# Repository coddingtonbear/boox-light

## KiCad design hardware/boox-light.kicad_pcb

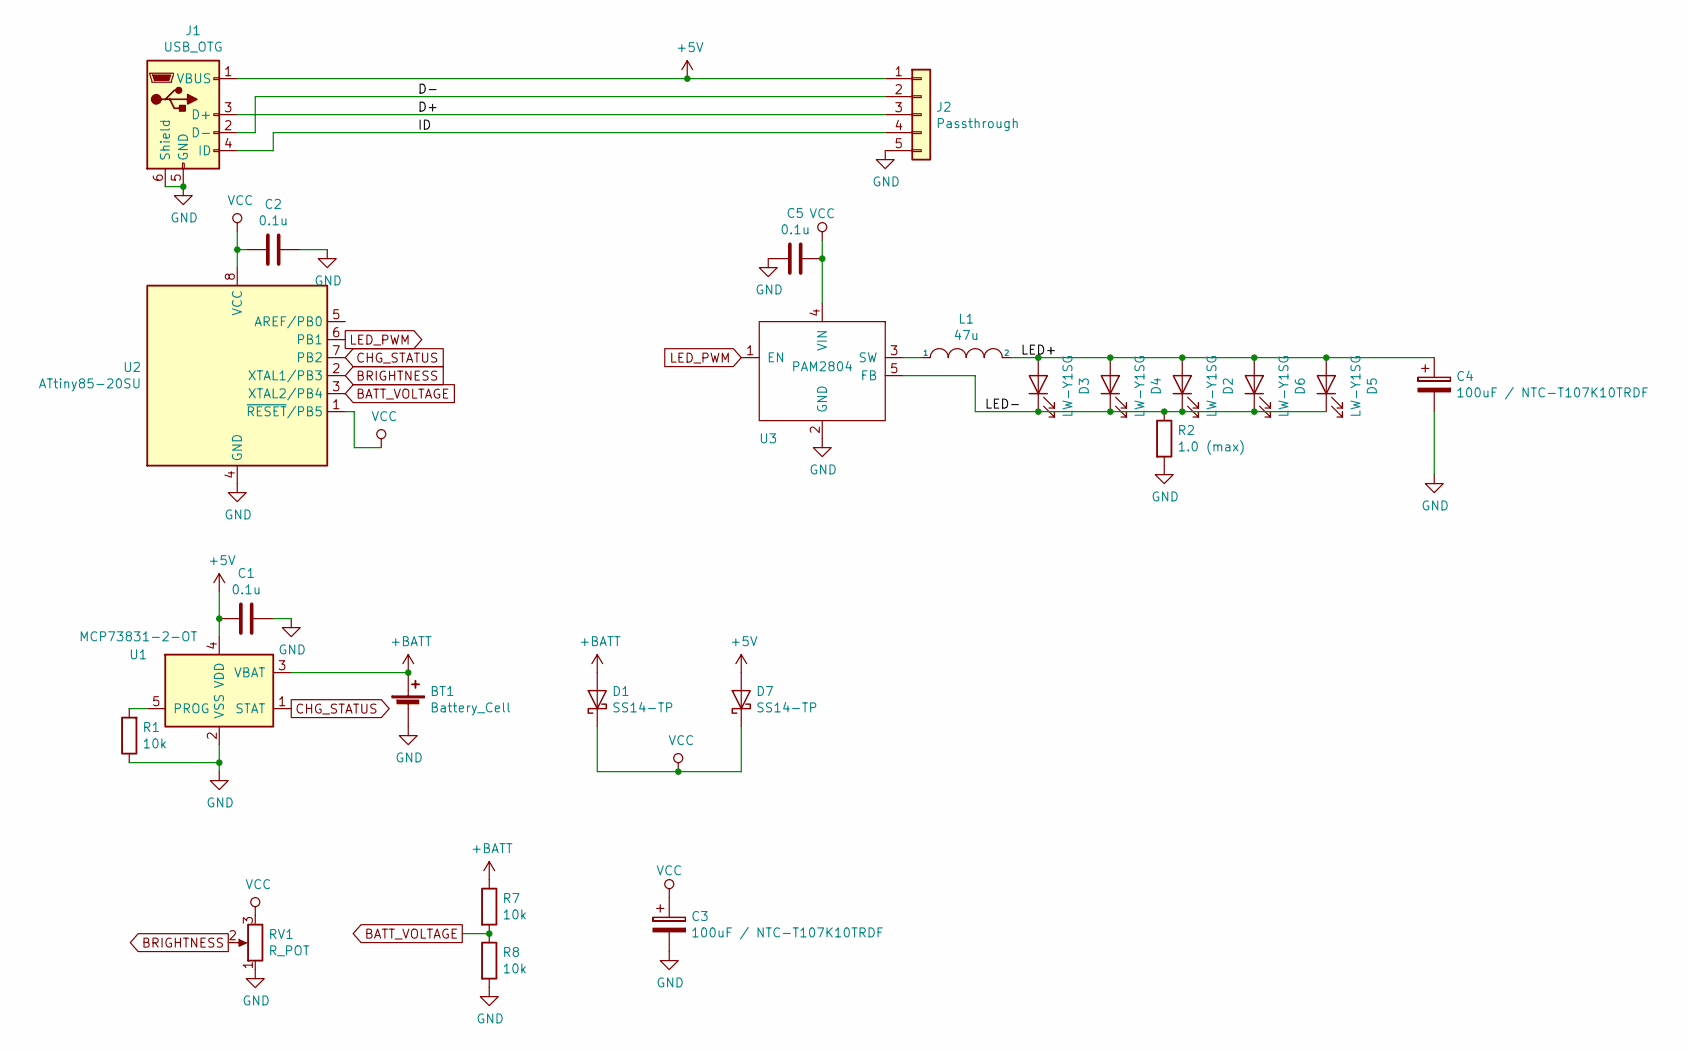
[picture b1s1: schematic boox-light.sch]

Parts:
BT1: Battery_Cell; JST_EH_B02B-EH-A_02x2.50mm_Straight_LargePads
C1, C2, C5: 0.1u; 0805_Milling
C3, C4: 100uF / NTC-T107K10TRDF; CP_Tantalum_Case-D_EIA-7343-31_Milling
D1, D7: SS14-TP; DO-214AC
D2, D3, D4, D5, D6: LW-Y1SG; MICRO_SIDELED_2808
J1: USB_OTG; UJ2-MIBH-4-SMT
J2: Passthrough; JST_XH_B05B-XH-A_05x2.50mm_Straight_LargePads
L1: 47u; L_Bourns-SRN4018
R1, R7, R8: 10k; 0805_Milling
R2: 1.0 (max); 0805_Milling
RV1: R_POT; SV01_Murata_Pot
U1: MCP73831-2-OT; SOT-23-5
U2: ATtiny85-20SU; SOIJ-8_5.3x5.3mm_P1.27mm
U3: PAM2804; TSOT-23-5_HandSoldering

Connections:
+5V: C1.2, D7.2 (A), J1.1 (VBUS), J2.1, U1.4 (VDD)
+BATT: BT1.1 (+), D1.2 (A), R7.1, U1.3 (VBAT)
/D+: J1.3 (D+), J2.3
/D-: J1.2 (D-), J2.2
/ID: J1.4 (ID), J2.4
/LED+: C4.1, D2.2 (A), D3.2 (A), D4.2 (A), D5.2 (A), D6.2 (A), L1.2
/LED-: D2.1 (K), D3.1 (K), D4.1 (K), D5.1 (K), D6.1 (K), R2.1, U3.5 (FB)
BATT_VOLTAGE: R7.2, R8.1, U2.3 (XTAL2/PB4)
BRIGHTNESS: RV1.2, U2.2 (XTAL1/PB3)
CHG_STATUS: U1.1 (STAT), U2.7 (PB2)
GND: BT1.2 (-), C1.1, C2.1, C3.2, C4.2, C5.2, J1.5 (GND), J1.6 (Shield), J2.5, R1.1, R2.2, R8.2, RV1.1, U1.2 (VSS), U2.4 (GND), U3.2 (GND)
LED_PWM: U2.6 (PB1), U3.1 (EN)
unnamed: L1.1, U3.3 (SW)
unnamed: R1.2, U1.5 (PROG)
VCC: C2.2, C3.1, C5.1, D1.1 (K), D7.1 (K), RV1.3, U2.1 (~RESET~/PB5), U2.8 (VCC), U3.4 (VIN)

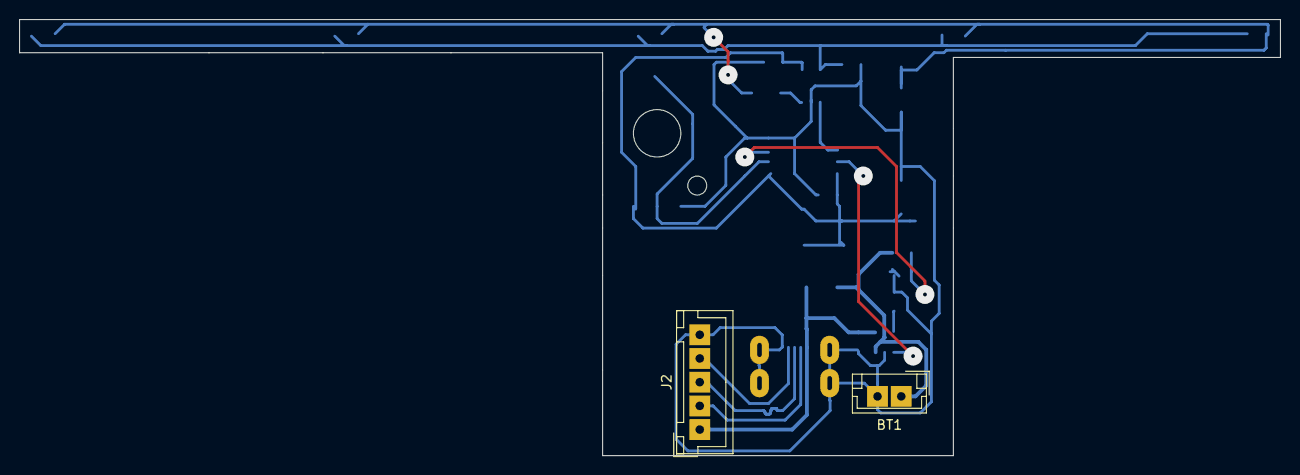
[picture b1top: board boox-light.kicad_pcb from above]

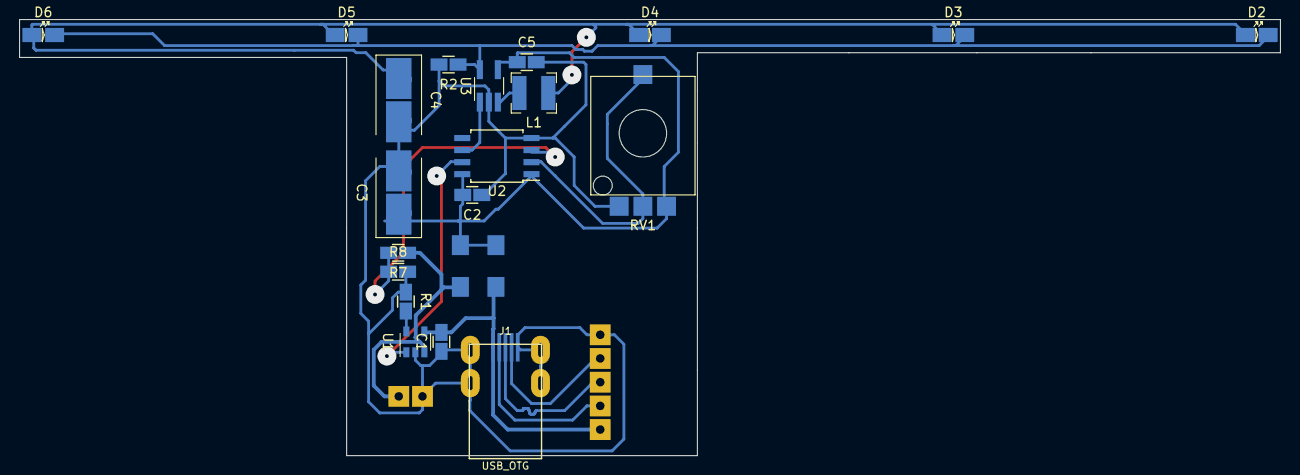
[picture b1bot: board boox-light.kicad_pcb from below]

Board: 2 copper layers, 133.0 x 46.0 mm, 24 parts (22 on the bottom side), 15 nets.

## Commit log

2018-09-28 And so it begins...
2018-09-30 Adding completed layout.
2018-09-30 Setting origin position.
